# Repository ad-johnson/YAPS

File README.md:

# YAPS
Bench top power supply

Schematics are in the Design folder

Custom footprints and symbols are in the Kicad folder: these will need downloading and their location added into the Kicad project's preferences: add location to Manage Symbol Libraries and Manage Footprint Libraries

LTSpice files are in the LTSpice file.  They are broken down into three parts: Power Stage; Control Stage and Combined.  AndrewsParts may need to be put into your LTSpice installation sym library, e.g. ~/Library/ApplicationSupport/LTSpice/lib/sym

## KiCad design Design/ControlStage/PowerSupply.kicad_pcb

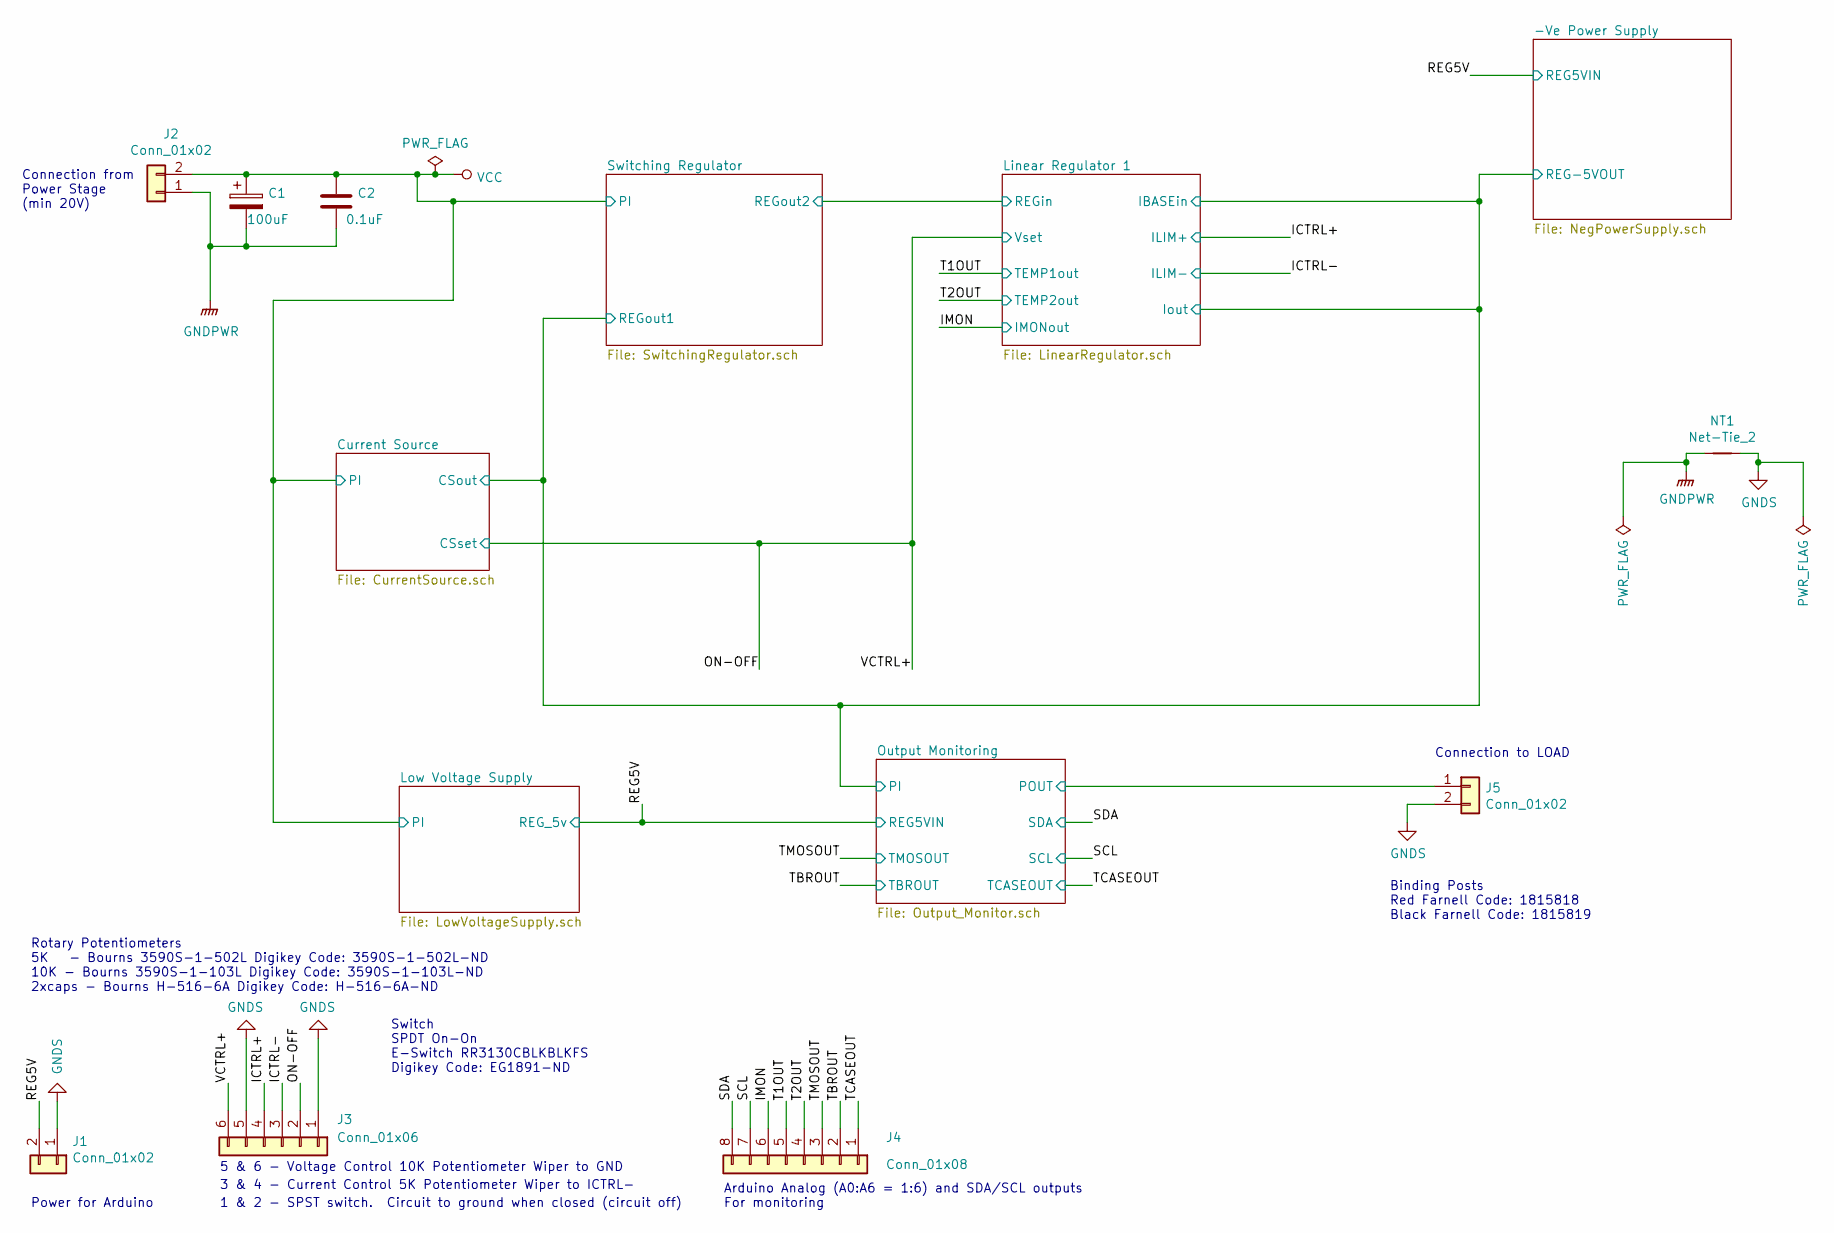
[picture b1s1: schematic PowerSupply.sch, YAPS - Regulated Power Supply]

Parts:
C1: 100uF; CP_Elec_8x10; Farnell Code 8823391
C2: 0.1uF; R_0805_2012Metric_Pad1.15x1.40mm_HandSolder; Farnell Code 2320839
J1: Conn_01x02; Molex_KK-254_AE-6410-02A_1x02_P2.54mm_Vertical; Digikey Code WM4111-ND + WM1575-ND + WM2623-ND
J2, J5: Conn_01x02; TerminalBlock_Phoenix_MKDS-1,5-2-5.08_1x02_P5.08mm_Horizont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
J3: Conn_01x06; Molex_KK-254_AE-6410-06A_1x06_P2.54mm_Vertical; Digikey Code WM4115-ND + WM1579-ND + WM2623-ND
J4: Conn_01x08; Molex_KK-254_AE-6410-08A_1x08_P2.54mm_Vertical; Digikey Code WM4117-ND + WM1581-ND + WM2623-ND
NT1: Net-Tie_2; NetTie-2_SMD_Pad2.0mm

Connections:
/ICTRL+: J3.4; also elsewhere on the board
/ICTRL-: J3.3; also elsewhere on the board
/IMON: J4.6; also elsewhere on the board
/ON-OFF: J3.2, J3.6; also elsewhere on the board
/Output Monitoring/POUT: J5.1; also elsewhere on the board
/REG5V: J1.2; also elsewhere on the board
/SCL: J4.7; also elsewhere on the board
/SDA: J4.8; also elsewhere on the board
/T1OUT: J4.5; also elsewhere on the board
/T2OUT: J4.4; also elsewhere on the board
/TBROUT: J4.2; also elsewhere on the board
/TCASEOUT: J4.1; also elsewhere on the board
/TMOSOUT: J4.3; also elsewhere on the board
GNDPWR: C1.2, C2.2, J2.1, NT1.1; also elsewhere on the board
GNDS: J1.1, J3.1, J3.5, J5.2, NT1.2; also elsewhere on the board
VCC: C1.1, C2.1, J2.2; also elsewhere on the board

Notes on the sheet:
Connection from Power Stage (min 20V)
5 & 6 - Voltage Control 10K Potentiometer Wiper to GND
Arduino Analog (A0:A6 = 1:6) and SDA/SCL outputs For monitoring
3 & 4 - Current Control 5K Potentiometer Wiper to ICTRL-
Connection to LOAD
1 & 2 - SPST switch. Circuit to ground when closed (circuit off)
Power for Arduino
Rotary Potentiometers 5K - Bourns 3590S-1-502L Digikey Code: 3590S-1-502L-ND 10K - Bourns 3590S-1-103L Digikey Code: 3590S-1-103L-ND 2xcaps - Bourns H-516-6A Digikey Code: H-516-6A-ND
Binding Posts Red Farnell Code: 1815818 Black Farnell Code: 1815819
Switch SPDT On-On E-Switch RR3130CBLKBLKFS Digikey Code: EG1891-ND

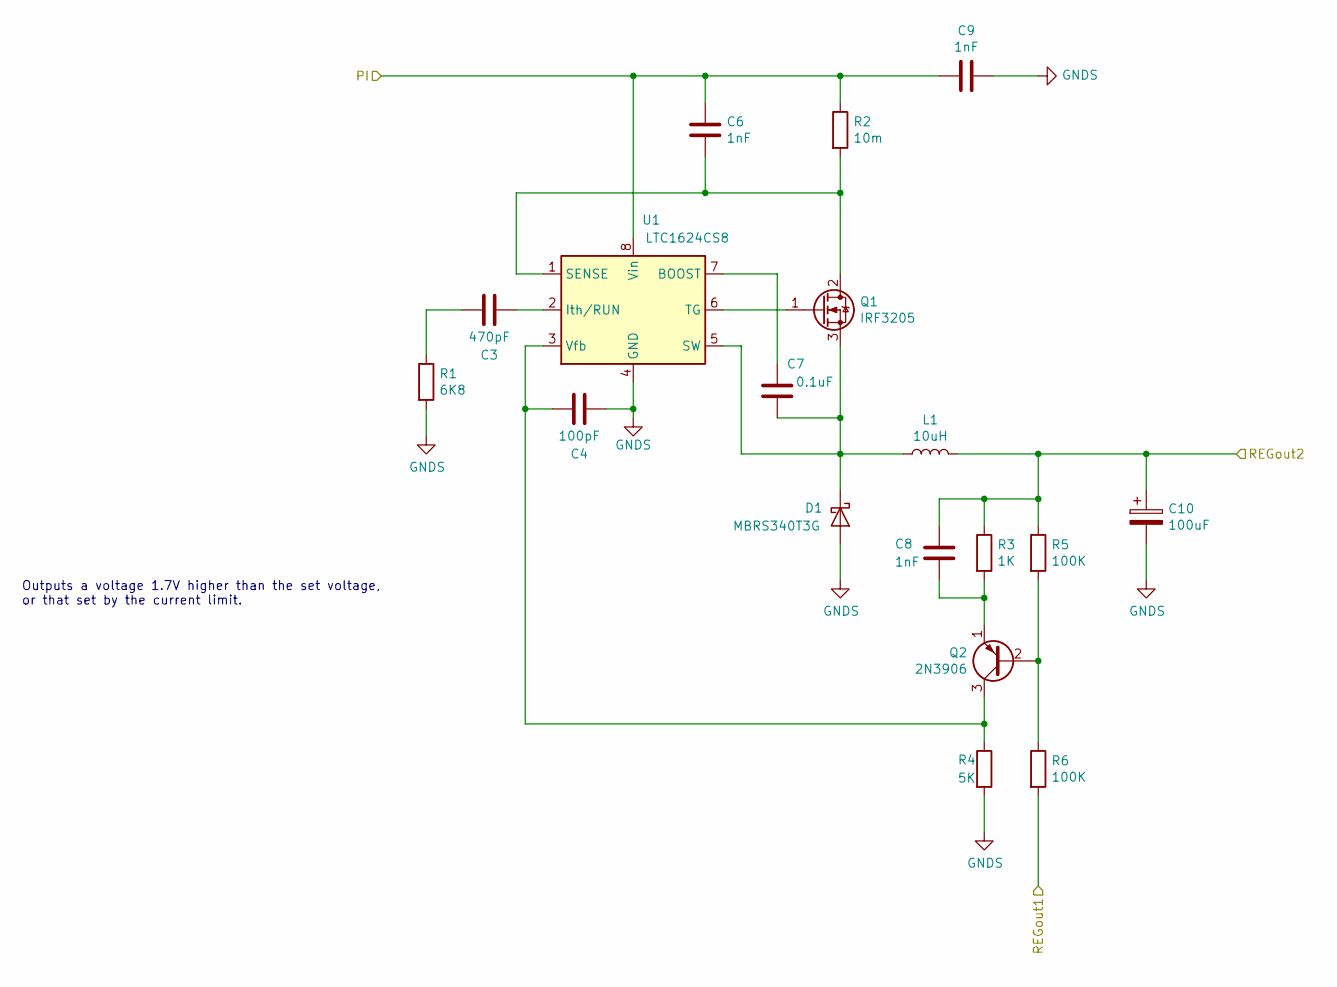
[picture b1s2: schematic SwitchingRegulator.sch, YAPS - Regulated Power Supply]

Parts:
C3: 470pF; C_0805_2012Metric_Pad1.15x1.40mm_HandSolder; Farnell Code 2896583
C4: 100pF; C_0805_2012Metric_Pad1.15x1.40mm_HandSolder; Farnell Code 2905173
C6, C8, C9: 1nF; C_0805_2012Metric_Pad1.15x1.40mm_HandSolder; Farnell Code 2320837
C7: 0.1uF; R_0805_2012Metric_Pad1.15x1.40mm_HandSolder; Farnell Code 2320839
C10: 100uF; CP_Elec_8x10; Farnell Code 8823391
D1: MBRS340T3G; D_SMC_Handsoldering; Farnell Code 9557377
L1: 10uH; L_Bourns_SRP1245A_Handsoldering; Farnell Code 2434072
Q1: IRF3205; TO-220-3_Vertical; Farnell Code 1704017
Q2: 2N3906; TO-92_Inline_Wide; Farnell Code 2453753
R1: 6K8; R_0805_2012Metric_Pad1.15x1.40mm_HandSolder; Farnell Code 2447711
R2: 10m; R_0805_2012Metric_Pad1.15x1.40mm_HandSolder; Digikey Code 1276-6156-1-ND
R3: 1K; R_0805_2012Metric_Pad1.15x1.40mm_HandSolder; Farnell Code 2447587
R4: 5K; R_0805_2012Metric_Pad1.15x1.40mm_HandSolder; Farnell Code 2616759
R5, R6: 100K; R_0805_2012Metric_Pad1.15x1.40mm_HandSolder; Farnell Code 2447551
U1: LTC1624CS8; SOIC-8_3.9x4.9mm_P1.27mm; Digikey Code LTC1624CS8#PBF-ND

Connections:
/Current Source/CSout: R6.2; also elsewhere on the board
/Linear Regulator 1/REGin: C8.1, C10.1, L1.2, R3.1, R5.1; also elsewhere on the board
GNDS: C4.1, C9.1, C10.2, D1.2 (A), R1.2, R4.2, U1.4 (GND); also elsewhere on the board
unnamed: C3.1, U1.2 (Ith/RUN)
unnamed: C3.2, R1.1
unnamed: C4.2, Q2.3 (C), R4.1, U1.3 (Vfb)
unnamed: C6.2, Q1.2 (D), R2.2, U1.1 (SENSE)
unnamed: C7.1, U1.7 (BOOST)
unnamed: C7.2, D1.1 (K), L1.1, Q1.3 (S), U1.5 (SW)
unnamed: C8.2, Q2.1 (E), R3.2
unnamed: Q1.1 (G), U1.6 (TG)
unnamed: Q2.2 (B), R5.2, R6.1
VCC: C6.1, C9.2, R2.1, U1.8 (Vin); also elsewhere on the board

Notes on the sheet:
Outputs a voltage 1.7V higher than the set voltage, or that set by the current limit.

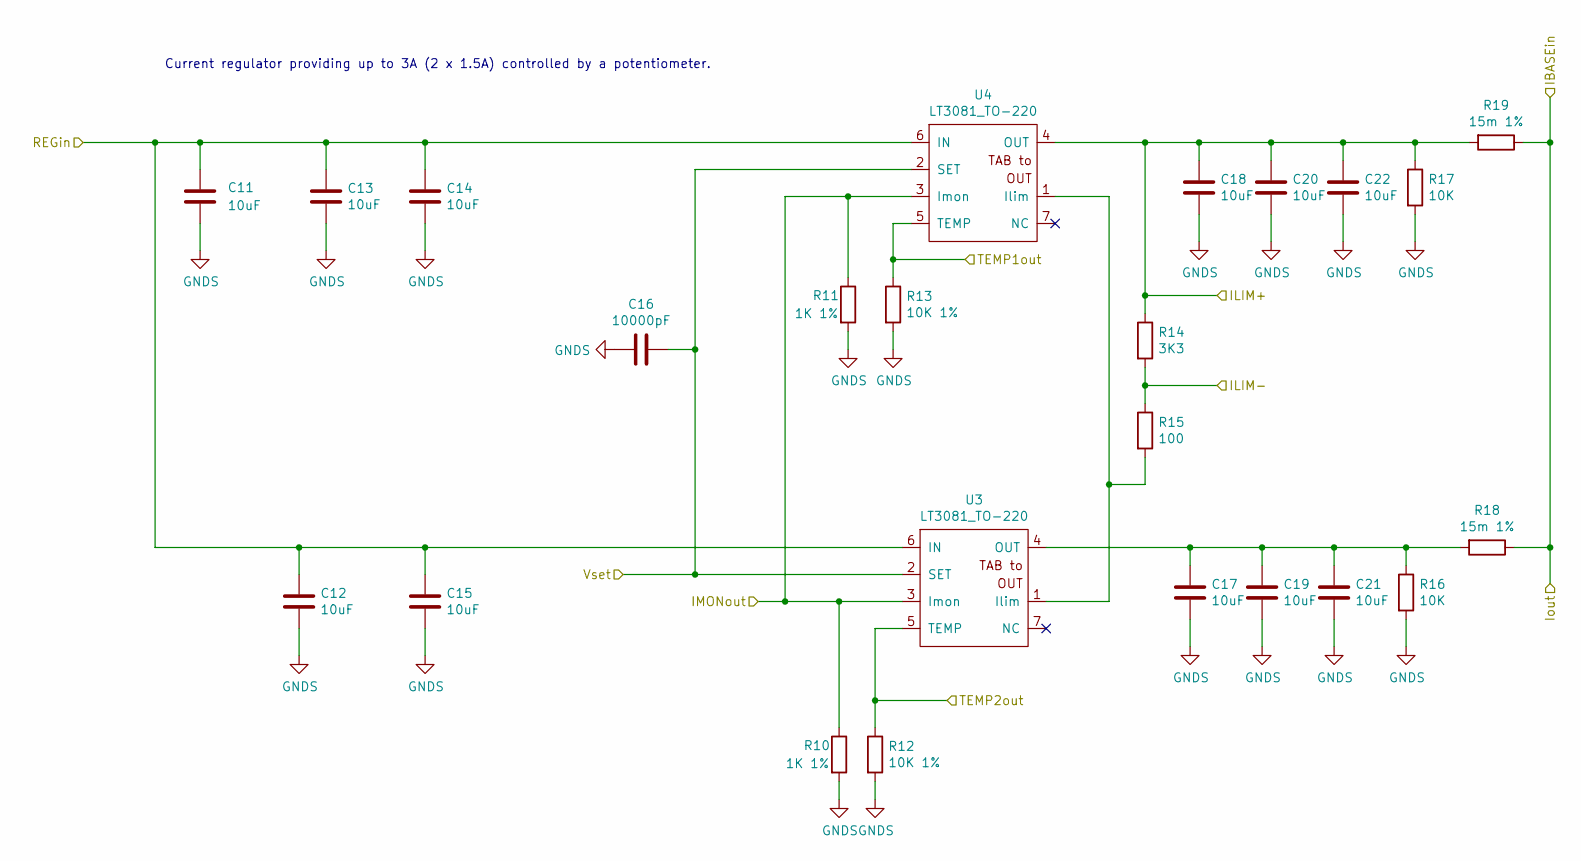
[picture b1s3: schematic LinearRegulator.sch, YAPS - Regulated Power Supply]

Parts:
C11, C12, C13, C14, C15, C17, C18, C19, C20, C21, C22: 10uF; C_0805_2012Metric_Pad1.15x1.40mm_HandSolder; Farnell Code 2611943
C16: 10000pF; C_0805_2012Metric_Pad1.15x1.40mm_HandSolder; Farnell Code 9406352
R10, R11: 1K 1%; R_0805_2012Metric_Pad1.15x1.40mm_HandSolder; Farnell Code 2447587
R12, R13: 10K 1%; R_0805_2012Metric_Pad1.15x1.40mm_HandSolder; Farnell Code 2694096
R14: 3K3; R_0805_2012Metric_Pad1.15x1.40mm_HandSolder; Farnell Code 1469911
R15: 100; R_0805_2012Metric_Pad1.15x1.40mm_HandSolder; Farnell Code 2447552
R16, R17: 10K; R_0805_2012Metric_Pad1.15x1.40mm_HandSolder; Farnell Code 2694096
R18: 15m 1%; R_0805_2012Metric_Pad1.15x1.40mm_HandSolder; Digikey code P19200CT-ND
R19: 15m 1%; R_0805_2012Metric_Pad1.15x1.40mm_HandSolder; Digikey Code P19200CT-ND
U3, U4: LT3081_TO-220; TO-220F-7_P2.54x3.7mm_StaggerOdd_Lead3.5mm_Vertical; Digikey Code LT3081ET7#PBF-ND

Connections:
/Current Source/CSout: R18.1, R19.1; also elsewhere on the board
/ICTRL+: C18.1, C20.1, C22.1, R14.1, R17.1, R19.2, U4.4 (OUT); also elsewhere on the board
/ICTRL-: R14.2, R15.1; also elsewhere on the board
/IMON: R10.1, R11.1, U3.3 (Imon), U4.3 (Imon); also elsewhere on the board
/Linear Regulator 1/REGin: C11.1, C12.1, C13.1, C14.1, C15.1, U3.6 (IN), U4.6 (IN); also elsewhere on the board
/ON-OFF: C16.1, U3.2 (SET), U4.2 (SET); also elsewhere on the board
/T1OUT: R13.1, U4.5 (TEMP); also elsewhere on the board
/T2OUT: R12.1, U3.5 (TEMP); also elsewhere on the board
GNDS: C11.2, C12.2, C13.2, C14.2, C15.2, C16.2, C17.2, C18.2, C19.2, C20.2, C21.2, C22.2, R10.2, R11.2, R12.2, R13.2, R16.2, R17.2; also elsewhere on the board
unnamed: C17.1, C19.1, C21.1, R16.1, R18.2, U3.4 (OUT)
unnamed: R15.2, U3.1 (Ilim), U4.1 (Ilim)

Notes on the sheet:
Current regulator providing up to 3A (2 x 1.5A) controlled by a potentiometer.

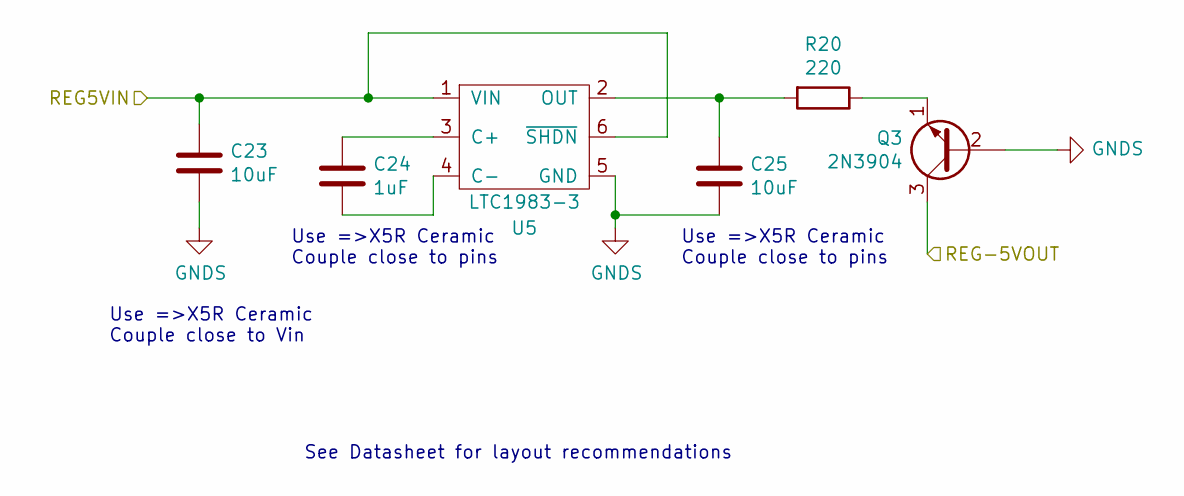
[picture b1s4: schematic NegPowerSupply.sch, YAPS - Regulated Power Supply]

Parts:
C23, C25: 10uF; C_0805_2012Metric_Pad1.15x1.40mm_HandSolder; Farnell Code 2611943
C24: 1uF; C_0805_2012Metric_Pad1.15x1.40mm_HandSolder; Farnell Code 2688485
Q3: 2N3904; TO-92_Inline; Farnell Code 1700648
R20: 220; R_0805_2012Metric_Pad1.15x1.40mm_HandSolder; Farnell Code 2447606
U5: LTC1983-3; TSOT-23-6_HandSoldering; Digikey Code LTC1983ES6-3#TRPBFCT-ND

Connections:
/Current Source/CSout: Q3.3 (C); also elsewhere on the board
/REG5V: C23.1, U5.1 (VIN), U5.6 (~SHDN); also elsewhere on the board
GNDS: C23.2, C25.2, Q3.2 (B), U5.5 (GND); also elsewhere on the board
unnamed: C24.1, U5.3 (C+)
unnamed: C24.2, U5.4 (C-)
unnamed: C25.1, R20.2, U5.2 (OUT)
unnamed: Q3.1 (E), R20.1

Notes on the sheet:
Use =>X5R Ceramic Couple close to pins
Use =>X5R Ceramic Couple close to Vin
See Datasheet for layout recommendations

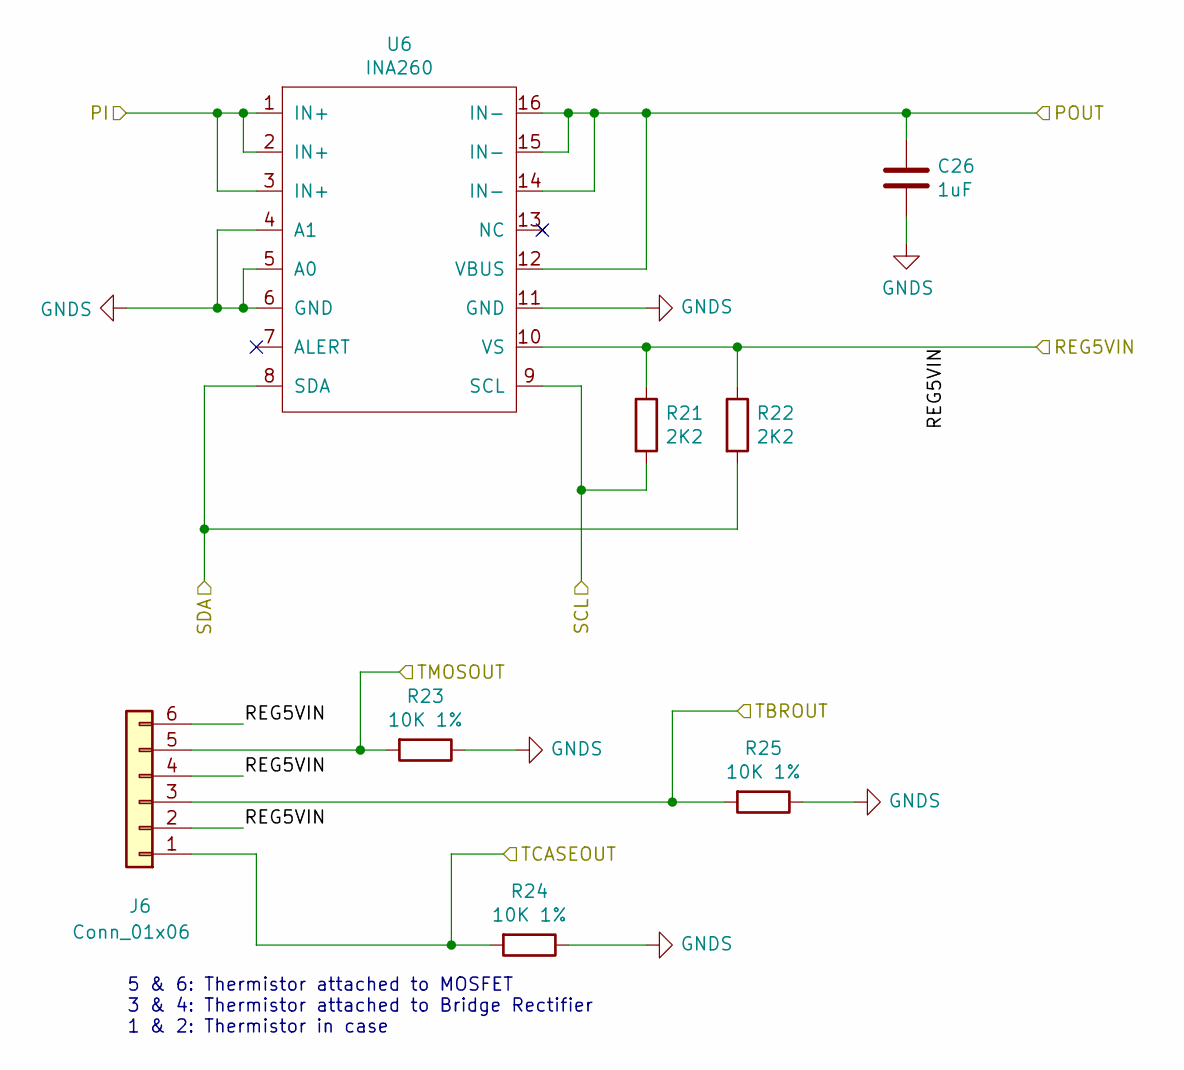
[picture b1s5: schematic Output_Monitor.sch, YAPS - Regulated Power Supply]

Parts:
C26: 1uF; C_0805_2012Metric_Pad1.15x1.40mm_HandSolder; Farnell Code 2688485
J6: Conn_01x06; Molex_KK-254_AE-6410-06A_1x06_P2.54mm_Vertical; Digikey Code WM4115-ND + WM1579-ND + WM2623-ND
R21, R22: 2K2; R_0805_2012Metric_Pad1.15x1.40mm_HandSolder
R23, R24, R25: 10K 1%; R_0805_2012Metric_Pad1.15x1.40mm_HandSolder; Farnell Code 2694096
U6: INA260; TSSOP-16_4.4x5mm_P0.65mm; Digikey Code 296-47777-1-ND

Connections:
/Current Source/CSout: U6.1 (IN+), U6.2 (IN+), U6.3 (IN+); also elsewhere on the board
/Output Monitoring/POUT: C26.1, U6.12 (VBUS), U6.14 (IN-), U6.15 (IN-), U6.16 (IN-); also elsewhere on the board
/REG5V: J6.2, J6.4, J6.6, R21.1, R22.1, U6.10 (VS); also elsewhere on the board
/SCL: R21.2, U6.9 (SCL); also elsewhere on the board
/SDA: R22.2, U6.8 (SDA); also elsewhere on the board
/TBROUT: J6.3, R25.2; also elsewhere on the board
/TCASEOUT: J6.1, R24.2; also elsewhere on the board
/TMOSOUT: J6.5, R23.2; also elsewhere on the board
GNDS: C26.2, R23.1, R24.1, R25.1, U6.4 (A1), U6.5 (A0), U6.6 (GND), U6.11 (GND); also elsewhere on the board

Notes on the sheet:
5 & 6: Thermistor attached to MOSFET 3 & 4: Thermistor attached to Bridge Rectifier 1 & 2: Thermistor in case

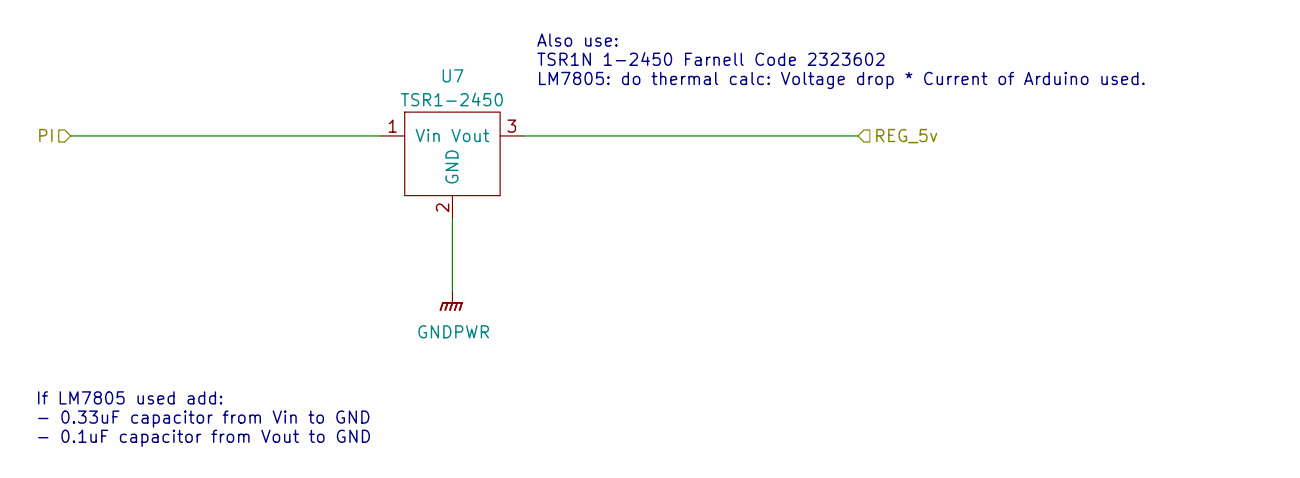
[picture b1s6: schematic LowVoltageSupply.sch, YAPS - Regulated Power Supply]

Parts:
U7: TSR1-2450; TSR1-24xx_TO-220-3

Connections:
/REG5V: U7.3 (Vout); also elsewhere on the board
GNDPWR: U7.2 (GND); also elsewhere on the board
VCC: U7.1 (Vin); also elsewhere on the board

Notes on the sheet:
Also use: TSR1N 1-2450 Farnell Code 2323602 LM7805: do thermal calc: Voltage drop * Current of Arduino used.
If LM7805 used add: - 0.33uF capacitor from Vin to GND - 0.1uF capacitor from Vout to GND

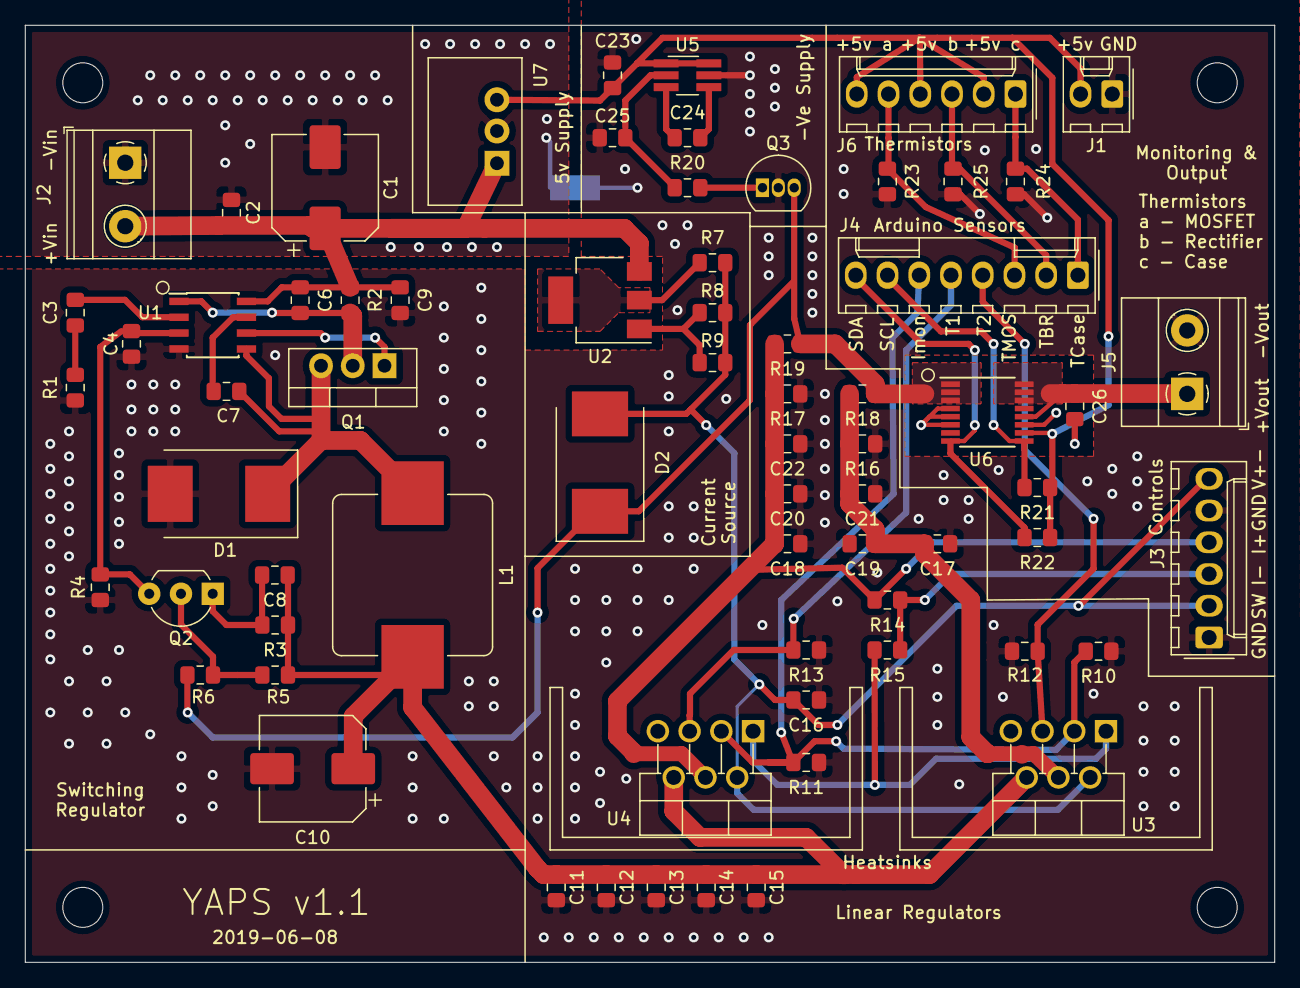
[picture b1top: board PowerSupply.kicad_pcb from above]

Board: 2 copper layers, 100.0 x 75.0 mm, 70 parts (1 on the bottom side), 35 nets.

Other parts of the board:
D2: MBRS340T3G; D_SMC_Handsoldering
R7: 200; R_0805_2012Metric_Pad1.15x1.40mm_HandSolder
R8: 47K5; R_0805_2012Metric_Pad1.15x1.40mm_HandSolder
R9: 73K2; R_0805_2012Metric_Pad1.15x1.40mm_HandSolder
U2: LT3092xSOT223; SOT-223-3_TabPin2

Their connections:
/Current Source/CSout: D2.1; also elsewhere on the board
/ON-OFF: D2.2, R7.1, R8.2, R9.2; also elsewhere on the board
unnamed: R7.2, U2.2
unnamed: R8.1, R9.1, U2.1
VCC: U2.3; also elsewhere on the board

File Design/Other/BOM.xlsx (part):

Name | Type | Ref - Control Stage | Ref - Power Stage | Reqd Qty | Order Qty | Mounting | Mfr | Mfr Part No. | Farnell Code | Digikey Code | CPC Code | Mouser Code | Datasheet | Notes
0.1uF | Capacitor | C2, C7 |  | 2 | 10 | 0805 | Multicomp | MC0805B104J500CT | 2320839 |  |  |  | Datasheet
100uF | Electrolytic | C1, C10 |  | 2 | 2 | 8x10 SMD | Nichicon | UUD1H101MNL1GS | 8823391 |  |  |  | Datasheet
6-way receptacle | CONNECTOR | J3, J6 |  | 2 | 2 | N/A | Molex | 22-01-2061 |  | WM1579-ND |  |  | Datasheet
6-way header | CONNECTOR | J3, J6 |  | 2 | 2 | TH | Molex | 22-27-2061 |  | WM4115-ND |  |  | Datasheet
2-way receptacle | CONNECTOR | J1 |  | 1 | 1 | N/A | Molex | 22-01-2021 |  | WM1575-ND |  |  | Datasheet
2-way header | CONNECTOR | J1 |  | 1 | 1 | TH | Molex | 22-27-2021 |  | WM4111-ND |  |  | Datasheet
8-way receptacle | CONNECTOR | J4 |  | 1 | 1 | N/A | Molex | 22-01-2081 |  | WM1581-ND |  |  | Datasheet
8-way header | CONNECTOR | J4 |  | 1 | 1 | TH | Molex | 22-27-2081 |  | WM4117-ND |  |  | Datasheet
Crimp | CONNECTOR | J1, J3, J4, J6 |  | 4 | 25 | N/A | Molex | 08-50-0032 |  | WM2623-ND |  |  | Datasheet
Current Source LT3092 | IC | U2 |  | 1 | 1 | SOT223 | Linear Technology | LT3092EST#TRPBF |  | LT3092EST#TRPBFCT-ND |  |  | Datasheet
Step Down Reg LTC1624 | IC | U1 |  | 1 | 1 | 8-SOIC | Linear Technology | LTC1624CS8#PBF |  | LTC1624CS8#PBF-ND |  |  | Datasheet
Linear Reg LT3081 | IC | U3, U4 |  | 2 | 2 | TO-220-7 | Linear Technology | LT3081ET7#PBF |  | LT3081ET7#PBF-ND |  |  | Datasheet
Switched Inv LTC1983-2 | IC | U5 |  | 1 | 1 | SOT226 | Linear Technology | LTC1983ES6-3#TRPBF |  | LTC1983ES6-3#TRPBFCT-ND |  |  | Datasheet
Pwr/Curr Monitor INA260 | IC | U6 |  | 1 | 1 | 16-TSSOP | TI | INA260AIPWR |  | 296-47777-1-ND |  |  | Datasheet
DC-DC Linear Converter 5V 1A | REGULATOR | U7 |  | 1 | 1 | SIP/TO-220 | Traco Power | TSRN 1-2450 | 2280247 |  |  |  | Datasheet | TSR 1-2450 also acceptable
470pF | Capacitor | C3 |  | 1 | 10 | 0805 | Vishay | VJ0805Y471JXAPW1BC | 2896583 |  |  |  | Datasheet
100pF | Capacitor | C4 |  | 1 | 10 | 0805 | Kemet | C0805C101J5RACAUTO | 2905173 |  |  |  | Datasheet
1000pF | Capacitor | C6, C8, C9 |  | 3 | 10 | 0805 | Multicomp | MC0805B102J500CT | 2320837 |  |  |  | Datasheet
10uF | Capacitor | C11, C12, C13, C14, C15, C17, C18, C19, C20, C21, C22, C23, C25 |  | 13 | 20 | 0805 | Murata | GRM21BR6YA106KE43L | 2611943 |  |  |  | Datasheet
1uF | Capacitor | C24, C26 |  | 2 | 5 | 0805 | Murata | GCM21BR71H105KA03L | 2688485 |  |  |  | Datasheet
6K8 | Resistor | R1 |  | 1 | 10 | 0805 | Multicomp | MCWR08X6801FTL | 2447711 |  |  |  | Datasheet
10m | Resistor | R2 |  | 1 | 5 | 0805 | Samsung | RU2012FR010CS |  | 1276-6156-1-ND |  |  | Datasheet
1K | Resistor | R3, R10, R11 |  | 3 | 10 | 0805 | Multicomp | MCWR08X1001FTL | 2447587 |  |  |  | Datasheet
5K | Resistor | R4 |  | 1 | 10 | 0805 | Vishay | CRCW08055K00FKTA | 2616759 |  |  |  | Datasheet
100K | Resistor | R5, R6 |  | 2 | 10 | 0805 | Multicomp | MCWR08X1003FTL | 2447551 |  |  |  | Datasheet
200 | Resistor | R7 |  | 1 | 10 | 0805 | Multicomp | MCWR08X2000FTL | 2447602 |  |  |  | Datasheet
47K5 | Resistor | R8 |  | 1 | 10 | 0805 | Multicomp | MCWR08X4752FTL | 2447665 |  |  |  | Datasheet
73K2 | Resistor | R9 |  | 1 | 10 | 0805 | Panasonic | ERJ6ENF7322V | 2303742 |  |  |  | Datasheet
1K 1% | Resistor | - |  |  | 0 | 0805 |  |  |  |  |  |  | Datasheet | See 1K resistor which is 1%
10K 1% | Resistor | R12, R13, R16, R17, R23, R24, R25 |  | 7 | 10 | 0805 | Multicomp | MCWF08P1002FTL | 2694096 |  |  |  | Datasheet
3K3 | Resistor | R14 |  | 1 | 10 | 0805 | Vishay | CRCW08053K30FKEA | 1469911 |  |  |  | Datasheet
100 | Resistor | R15 |  | 1 | 10 | 0805 | Multicomp | MCWR08X1000FTL | 2447552 |  |  |  | Datasheet
10K | Resistor | - |  |  | 0 | 0805 |  |  |  |  |  |  | Datasheet | See 10K resistor which is 1%
15m 1% | Resistor | R18, R19 |  | 2 | 5 | 0805 | Panasonic | ERJ-6CWFR015V |  | P19200CT-ND |  |  | Datasheet
220 | Resistor | R20 |  | 1 | 10 | 0805 | Multicomp | MCWR08X2200FTL | 2447606 |  |  |  | Datasheet
2K2 | Resistor | R21, R22 |  | 2 | 10 | 0805 | Multicomp | MCWR08X2201FTL | 2447623 |  |  |  | Datasheet
Schottky Rectifier | RECTIFIER | D1, D2 |  | 2 | 5 | SMC - 2 Lead | ON Semiconductor | MBRS340T3G | 9557377 |  |  |  | Datasheet
NPN Mosfet | MOSFET | Q1 |  | 1 | 5 | TO-220 | Infineon | IRF3205PBF | 1704017 |  |  |  | Datasheet
2N3906 PNP Bipolar | TRANSISTOR | Q2 |  | 1 | 5 | TO-92 | On Semiconductor | 2N3906TA | 2453753 |  |  |  | Datasheet
10uH Inductor | INDUCTOR | L1 |  | 1 | 1 | SMD Lead Frame | Bourns | SRP1265A-100M | 2434072 |  |  |  | Datasheet
2N3904 NPN Bipolar | TRANSISTOR | Q3 |  | 1 | 5 | TO-92 | On Semiconductor | 2N3904BU | 1700648 |  |  |  | Datasheet
10000pF | Capacitor | C16 |  | 1 | 10 | 0805 | Multicomp | MCU0805R103KCT | 9406352 |  |  |  | Datasheet
10K 10 Turn Potentiometer | POTENTIOMETER | Enclosure |  | 1 | 1 | Panel | Bourns | 3590S-1-103L |  | 3590S-1-103L-ND |  |  | Datasheet
5K 10 Turn Potentiometer | POTENTIOMETER | Enclosure |  | 1 | 1 | Panel | Bourns | 3590S-1-502L |  | 3590S-1-502L-ND |  |  | Datasheet
Rotary Dial | KNOB | Enclosure |  | 2 | 2 | N/A | Bourns | HH-516-6A |  | HH-516-6A-ND |  |  | Datasheet
Red Binding Post | CONNECTOR | Enclosure |  | 1 | 1 | Panel | Cliff Electronic Components | TP1 Red | 1815818 |  |  |  | Datasheet
Black Binding Post | CONNECTOR | Enclosure |  | 1 | 1 | Panel | Cliff Electronic Components | TP1 Black | 1815819 |  |  |  | Datasheet
10R 100W Power Resistor | Resistor | OPTIONAL FOR TESTING |  | 0 | 1 | N/A | CGS-TE Connectivity | HSC10010RJ |  |  | RE03534 |  | Datasheet
SPDT Switch | SPDT | Enclosure |  | 1 | 1 | Panel | E-Switch | RR3130CBLKBLKFS |  | EG1891-ND |  |  | Datasheet
60VA 9-0-9 3.3A | TRANSFORMER |  | Enclosure | 1 | 1 | Panel | Multicomp | MCTA060/09 |  |  | FF01551 |  | Datasheet
Terminal Block, 2-way | CONNECTOR | J2, J5 | J1, J2 | 4 | 4 |  | Phoenix Contact | 1729128 |  |  | CN14697 |  | Datasheet
Bridge Rectifier | RECTIFIER |  | D1 | 1 | 1 | TH | Taiwan Semiconductor | GBU603 |  |  | SC09284 |  | Datasheet
Smoothing Capacitor | Capacitor |  | C1, C2 | 2 | 2 | TH | Multicomp | LPR50V478M30X25 |  |  | CA04834 |  | Datasheet
Bleed Resistor | Resistor |  | R1 | 1 | 10 | TH | TT Electronics | MFP1-10K JI |  |  | RE05119 |  | Datasheet
Slow blow Fuse | FUSE |  | Enclosure | 1 | 10 | N/A | Littelfuse | 021502.5P |  |  | FF02710 |  | Datasheet
Switch&plug | CONNECTOR |  | Enclosure | 1 | 1 | Panel | Bulgin | BZH01/Z0000/01 |  |  | CN01731 |  | Datasheet
Mains plug&lead | CONNECTOR |  | Enclosure | 1 | 1 | N/A | Pro Elect | PE01086 |  |  | PL13317 |  | Datasheet
Thermal Paste | HEATSINK | Consumable |  | 1 | 1 | N/A | Servisol | 200001000 25GM |  |  | SAHEATSINKCOMP |  | Datasheet
Insulating Bushes | HEATSINK | Consumable |  | 3 | 10 | N/A | Unbranded | 31-35-25GFN |  |  | SC01134 |  | Datasheet
Mounting screws | HEATSINK | Consumable |  | 3 | 15 | M3 | Multicomp | MK3311 | 520160 |  |  |  | Datasheet
TO220 Heatsink | HEATSINK | U3, U4 |  | 2 | 2 | TO-220 | FischerElektronik | FK 214 SA-CB |  |  | SC10835 |  | Datasheet | For LT3081, 15 c/w
TO220 heatsink | HEATSINK |  | D1 | 1 | 1 | N/A | Aavid Thermalloy | 1.25GY-50 |  |  | SC10807 |  |  | For GBU603, 8.6c/w. Needs adjusting as it has a groove for TO220 in the middle.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
PCB Mounts | MOUNT | Enclosure |  | 8 | 10 | N/A | Duratool | D01468 |  |  | PC01634 |  | Datasheet
Ring crimp terminals | MOUNT |  | Enclosure | 1 | 10 | M3 | JST | LRB-2.5TM3 |  |  | CN16906 |  | Datasheet
10K Thermistor | THERMISTOR | J6 |  | 3 | 3 | TH | Ametherm | PANE 103395-410 |  | 570-1065-ND |  |  | Datasheet
4Duino | Micro + LED | Enclosure |  | 1 | 1 | N/A | 4D systems | SK-4Duino-24 |  |  |  | 971-SK-4DUINO-24 | Datasheet | Starter kit. Could use a Leonardo and separate LCD. Design uses all 6 Analog in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
Assumes that transformer is being used for Power Stage. If a different supply i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

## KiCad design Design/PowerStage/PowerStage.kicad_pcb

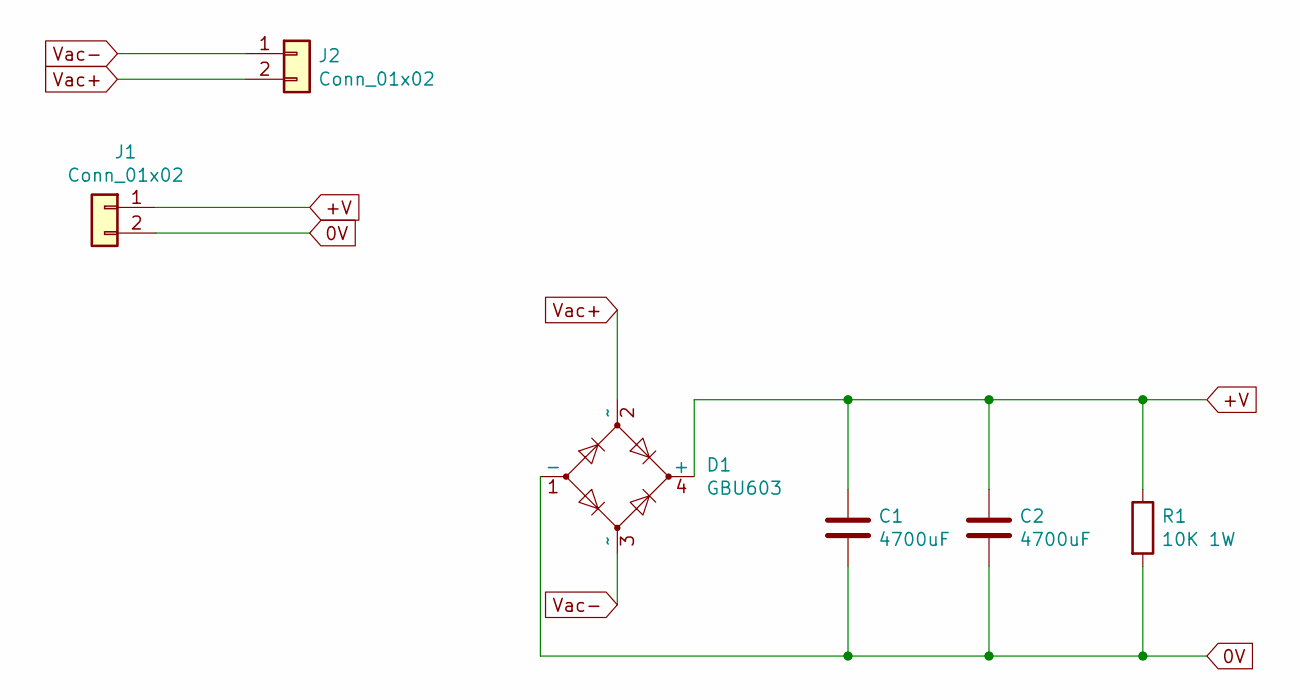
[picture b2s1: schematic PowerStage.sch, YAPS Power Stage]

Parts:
C1, C2: 4700uF; CP_Radial_D30.0mm_P10.00mm_SnapIn
D1: GBU603; Diode_Bridge_23.0x3.5mm_P5.0mm
J1, J2: Conn_01x02; TerminalBlock_Phoenix_MKDS-1,5-2-5.08_1x02_P5.08mm_Horizont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
R1: 10K 1W; R_Axial_DIN0207_L6.3mm_D2.5mm_P10.16mm_Horizontal

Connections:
0V: C1.2, C2.2, D1.1 (-), J1.2, R1.2
+V: C1.1, C2.1, D1.4 (+), J1.1, R1.1
Vac+: D1.2 (~~), J2.2
Vac-: D1.3 (~~), J2.1

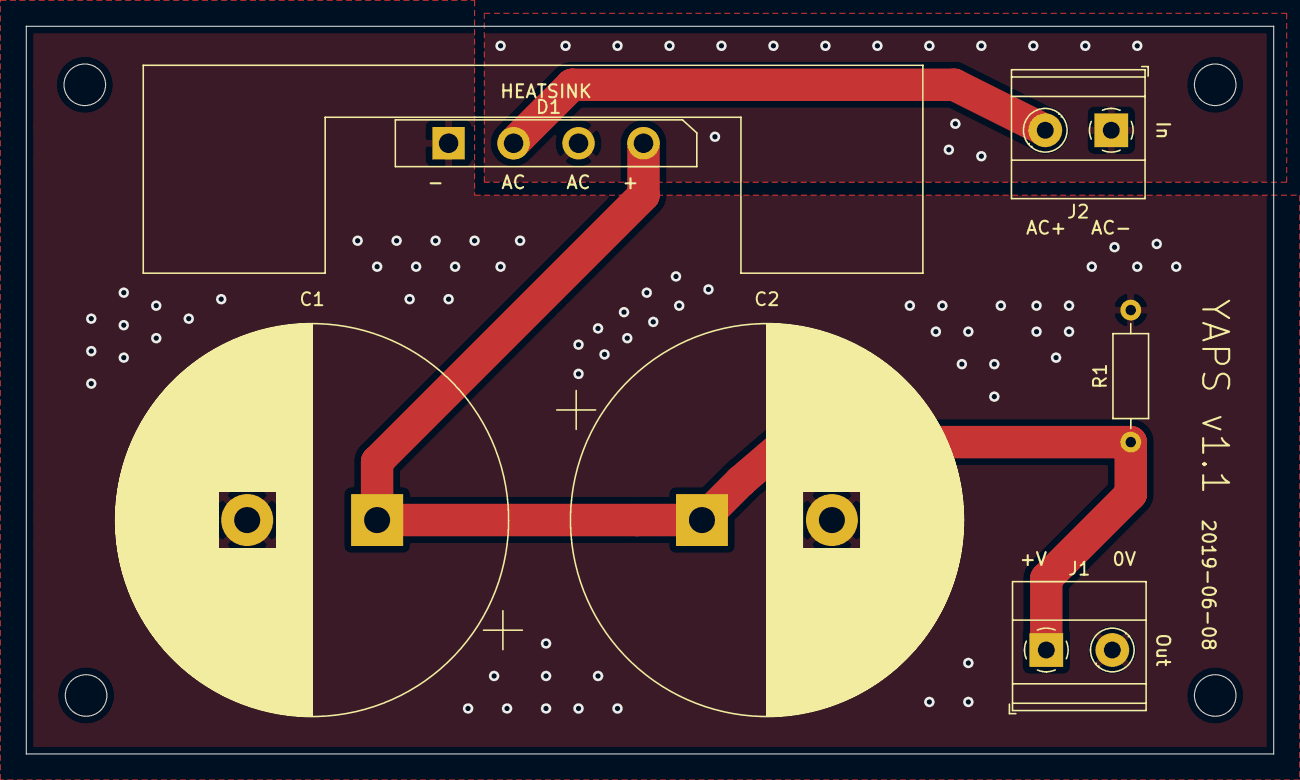
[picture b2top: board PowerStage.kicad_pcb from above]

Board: 2 copper layers, 96.0 x 56.0 mm, 6 parts (0 on the bottom side), 4 nets.

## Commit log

2019-05-28 Add files via upload
    LTSpice Files. AndrewsParts may need to be moved to your LTSpice sym library (on Mac OS: ~/Library/LTSpice/lib/sym
2019-05-28 Add files via upload
    KiCad 5 schematics
2019-05-28 Add files via upload
    Custom symbols and footprints. Will need to be added to paths to open schematics and PCBNew
2019-05-28 Update README.md
    Updated
